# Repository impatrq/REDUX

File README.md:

2<div align="center">

</div>

<div align="center">

# REDUX: Órtesis activa de codo para rehabilitación traumatológica

</div>

<div align="center">

</div>

## 🔗 Repositorio y Redes:

## 🗓️ Objetivo del Proyecto:

El nombre **REDUX** proviene del latín y significa *"restauración"* o *"retorno"*. El objetivo general del proyecto es desarrollar un prototipo funcional, seguro y de costo accesible de órtesis activa de codo que asista los movimientos de flexión y extensión a partir de la señal electromiográfica de superficie (sEMG) del bíceps y del tríceps, con registro digital de cada sesión para su uso bajo supervisión profesional en consultorios de kinesiología.

## 🌎 Visión a futuro e Impacto esperado

REDUX busca ser una herramienta de apoyo para el kinesiólogo, no un reemplazo. Al asistir según el esfuerzo muscular real del paciente, reduce la fatiga, evita compensaciones musculares perjudiciales y permite registrar de forma objetiva la evolución (rango de movimiento y porcentaje de asistencia sesión a sesión). A futuro, la arquitectura abierta y accesible permite proyectar mejoras como control de posición, rutinas preprogramadas, extensión a otras articulaciones y ensayos con usuarios.

## 💭 ¿De dónde surgió la idea?

Los procesos de rehabilitación traumatológica del miembro superior (fracturas, luxaciones, traumatismos o cirugías) requieren numerosas sesiones repetitivas donde el profesional guía manualmente el brazo y registra mediciones puntuales, mientras que los exoesqueletos robóticos comerciales tienen costos elevados que dificultan su adopción en consultorios y centros de nuestra región. En el marco de las Prácticas Profesionalizantes de la especialidad Aviónica de la **E.E.S.T. N°7 "Taller Regional Quilmes" (IMPA)**, el equipo desarrolló una alternativa integral, segura y accesible.

## 🖐 Descripción del proyecto:

REDUX se compone de cuatro subsistemas físicos y una plataforma web remota:

* **Órtesis:** estructura impresa en 3D (diseño preliminar en Onshape y definitivo en AutoCAD) fijada a brazo y antebrazo mediante tiras elásticas y velcro, con topes mecánicos rígidos en la articulación y un encoder magnético absoluto **AS5600** (`I2C` a 400 kHz, 12 bits) que mide el ángulo articular.
* **Unidad de accionamiento:** motor de corriente continua de 12 V con reductora (30 RPM) montado externamente para reducir el peso en el brazo y aislar el ruido eléctrico, transmitiendo fuerza mediante un carrete y un sistema de poleas.
* **Unidad electrónica:** centrada en una **Raspberry Pi Pico 2 W (RP2350)** con firmware en **C11** sobre **Pico SDK 2.x** y lazo determinista de 1 ms (Núcleo 0 dedicado al control y Núcleo 1 a la interfaz). Integra dos cadenas analógicas de acondicionamiento sEMG (preamplificación con **AD620**, filtros activos Sallen-Key pasa-altos ~20 Hz y pasa-bajos ~500 Hz con **TL084**, rectificación de precisión de onda completa y circuito **RLD** con resistencia de seguridad de 4,7 a 10 MΩ), etapa de potencia con puente H **BTS7960** (PWM de 20 kHz) y aislación galvánica mediante optoacopladores **6N137**, separación de masas (`GND1` potencia y `GND2` lógica/señal) y fuentes aisladas (**LM2596** y **B0505S**).
* **Panel de control:** soporte inclinado a 35° con pantalla **TFT ST7735** (1,44", 128x128, `SPI1`) programada con **LVGL 8.3.11** (diseñada en SquareLine Studio) y teclado matricial de membrana **4x4**, comunicándose mediante colas para calibrar el rango articular y los umbrales de reposo/MVC en cada sesión, iniciar/finalizar sesiones y visualizar fallas o telemetría.
* **Plataforma web y gestión de datos:** aplicación **Flask** con **SQLite** y **SQLAlchemy**, interfaz en **HTML**, **Bootstrap 5** y **Chart.js**, autenticación con roles (`médico/kinesiólogo` y `paciente`), envío HTTP autenticado (`X-Redux-Key`) con `id_envio` idempotente y pruebas automáticas con `pytest`.

En operación, la lógica de intención evalúa la activación muscular mediante compuerta **XOR** entre bíceps y tríceps: asiste flexión o extensión de forma proporcional al esfuerzo y detiene/frena el motor ante reposo, co-contracción, límites articulares o fallas detectadas por la máquina de estados y el watchdog de 500 ms.

## 🛠️ Componentes principales:

| Componente | Función / Especificación |
| :--- | :--- |
| **Raspberry Pi Pico 2 W (RP2350)** | Microcontrolador principal (Cortex-M33, Wi-Fi, ADC interno, PWM, I2C, SPI) |
| **Encoder magnético AS5600** | Medición angular absoluta sin contacto de 12 bits vía I2C (0x36) |
| **Amplificadores de instrumentación AD620** | Preamplificación y ganancia diferencial de señales sEMG |
| **Amplificadores operacionales TL084** | Filtros activos pasa-altos/pasa-bajos, rectificador de precisión y RLD |
| **Electrodos descartables Ag/AgCl** | Adquisición superficial diferencial en bíceps y tríceps + referencia RLD |
| **Puente H BTS7960** | Control de motor DC 12 V (30 RPM) mediante señales PWM de 20 kHz |
| **Optoacopladores 6N137** | Aislación de señales PWM entre etapas de lógica y potencia |
| **Convertidores de alimentación / aislación** | LM2596, convertidor aislado B0505S y etapas ±5 V para analógica |
| **Pantalla TFT ST7735 + Teclado 4x4** | Interfaz local de calibración, control de sesión y diagnóstico |
| **Piezas impresas en 3D** | Estructura de órtesis, soporte de motor, carrete, caja electrónica y panel |

## 🧑🏽‍💻 Integrantes

| Integrantes | Responsabilidades | 
| :--- | :--- | 
| Bajales Ignacio | Gestion de Redes |
| Ramirez Hillz Benicio| Desarrollo de software |  
| Relañez Joaquin| Diseño de circuitos electronicos | 
| Gomez Facundo| Diseño de Placas electronicas | 
| Strangio Gael| Diseño 3D de eswtructura | 

## 🤝 Colaboración y Agradecimientos:

Este prototipo forma parte de las Prácticas Profesionalizantes de la especialidad Aviónica de la **E.E.S.T. N°7 "Taller Regional Quilmes" (IMPA)**. Agradecemos especialmente a nuestro sponsor, la **Universidad Argentina de la Empresa (UADE)**, por el asesoramiento, el espacio de trabajo y la impresión 3D de la estructura de la órtesis, así como a los docentes tutores y a toda la comunidad educativa.

Si deseas colaborar con **REDUX**, puedes aportar en:

- Perfeccionamiento del código y validaciones clínicas/técnicas.
- Mejora de hardware, PCB SMD y fabricación mecánica.
- Documentación técnica, manuales y ensayos de laboratorio.
- Apoyo institucional o financiero para investigación y desarrollo.

## 📱 Contactanos:

## 📱 Contactos personales

| Integrante | Gmail | LinkedIn |
| :--- | :--- | :--- |
| ** ** | | |
| ** ** | | |
| ** ** | | |
| ** ** | | |
| ** ** | | |

---

```[cite: 1, 5, 6, 7, 8, 9, 10, 11, 12, 13, 14, 15, 16, 17, 18, 19, 20, 21, 22, 23, 24, 25, 26, 27, 28, 29]

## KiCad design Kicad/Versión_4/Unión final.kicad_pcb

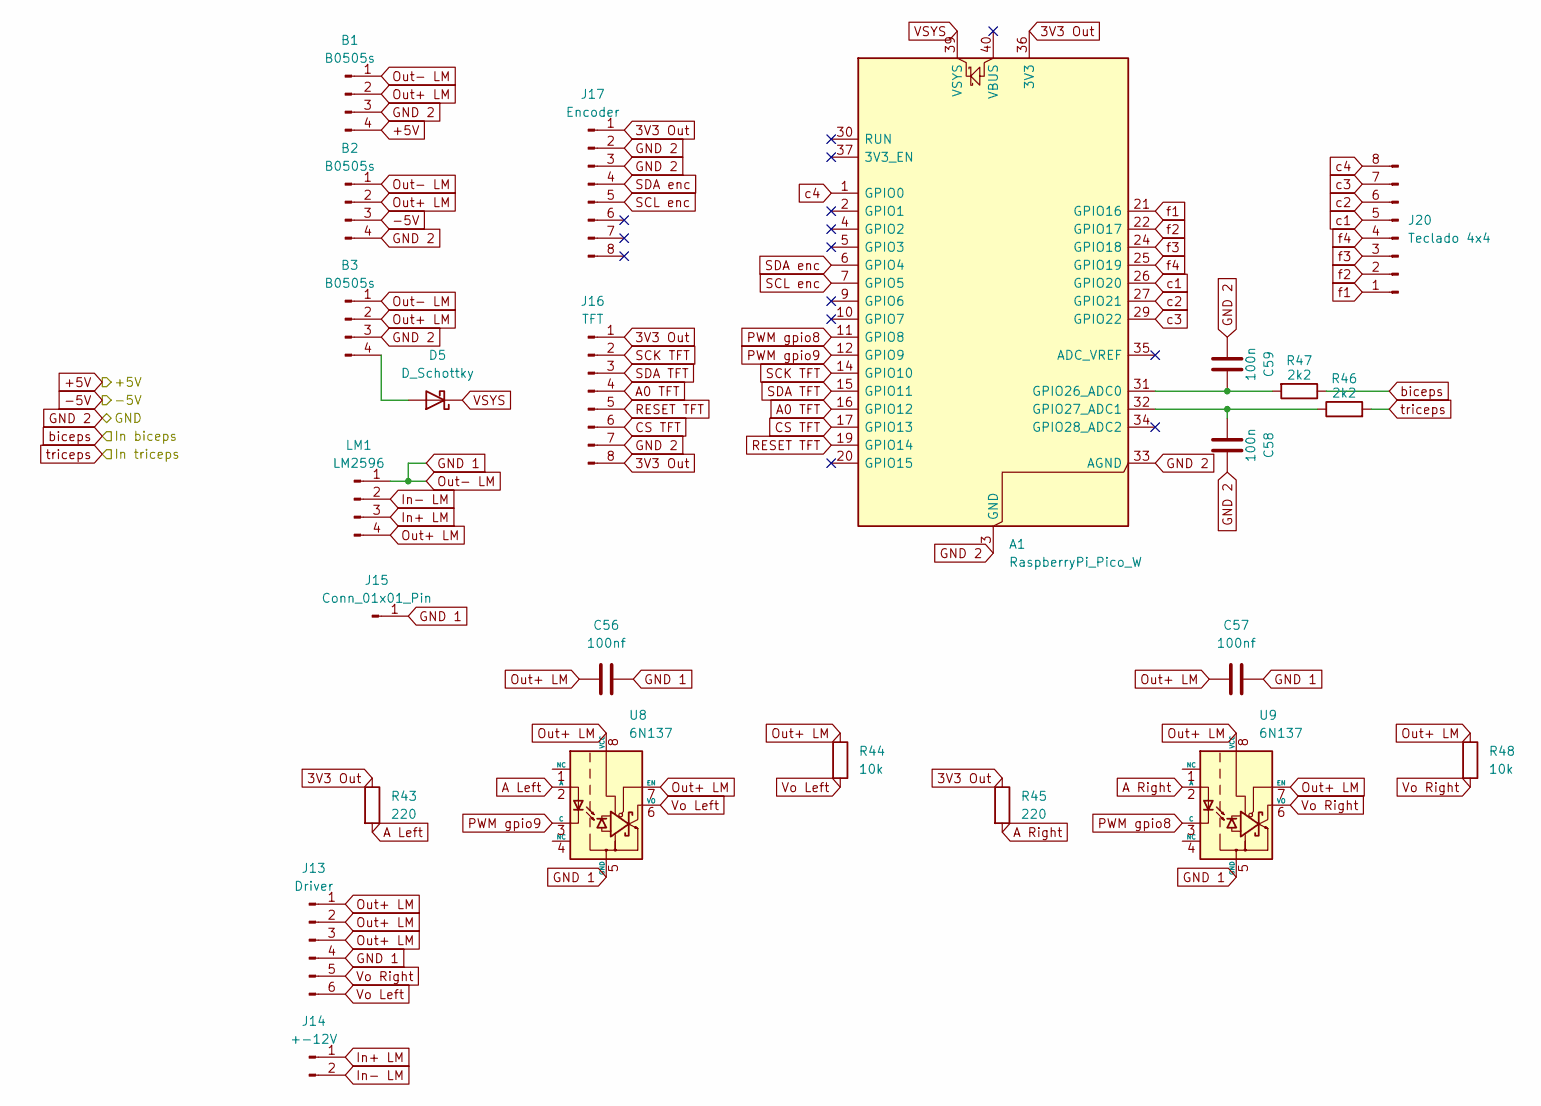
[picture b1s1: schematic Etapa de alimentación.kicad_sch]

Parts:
A1: RaspberryPi_Pico_W; RaspberryPi_Pico_Common_THT
B1, B2, B3: B0505s; B0505S-1w
C56, C57: 100nf; C_Disc_D10.0mm_W2.5mm_P5.00mm
C58, C59: 100n; C_0805_2012Metric_Pad1.18x1.45mm_HandSolder
D5: D_Schottky; D_DO-41_SOD81_P10.16mm_Horizontal
J13: Driver; PinHeader_1x06_P2.54mm_Vertical
J14: +-12V; TerminalBlock_MetzConnect_Type011_RT05502HBLC_1x02_P5.00mm_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
J15: Conn_01x01_Pin; PinHeader_1x01_P2.54mm_Vertical
J16: TFT; PinHeader_1x08_P2.54mm_Vertical
J17: Encoder; Molex_KK-254_AE-6410-08A_1x08_P2.54mm_Vertical
J20: Teclado 4x4; PinHeader_1x08_P2.54mm_Vertical
LM1: LM2596
R43, R45: 220; R_Axial_DIN0207_L6.3mm_D2.5mm_P10.16mm_Horizontal
R44, R48: 10k; R_Axial_DIN0207_L6.3mm_D2.5mm_P10.16mm_Horizontal
R46, R47: 2k2; R_Axial_DIN0207_L6.3mm_D2.5mm_P10.16mm_Horizontal
U8, U9: 6N137; DIP-8_W7.62mm

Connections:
3V3 Out: A1.36 (3V3), J16.1, J16.8, J17.1, R43.1, R45.1
+5V: B1.4; also elsewhere on the board
-5V: B2.3; also elsewhere on the board
A0 TFT: A1.16 (GPIO12), J16.4
A Left: R43.2, U8.2 (A)
A Right: R45.2, U9.2 (A)
CS TFT: A1.17 (GPIO13), J16.6
GND 1: B1.1, B2.1, B3.1, C56.2, C57.2, J13.4, J15.1 (Pin_1_1), LM1.1, U8.5 (GND), U9.5 (GND)
GND 2: A1.3 (GND), A1.8 (GND), A1.13 (GND), A1.18 (GND), A1.23 (GND), A1.28 (GND), A1.33 (AGND), A1.38 (GND), B1.3, B2.4, B3.3, C58.2, C59.1, J16.7, J17.2, J17.3; also elsewhere on the board
In+ LM: J14.1, LM1.3
In- LM: J14.2, LM1.2
unnamed: A1.31 (GPIO26_ADC0), C59.2, R47.2
unnamed: A1.32 (GPIO27_ADC1), C58.1, R46.1
unnamed: B3.4, D5.2 (A)
Out+ LM: B1.2, B2.2, B3.2, C56.1, C57.1, J13.1, J13.2, J13.3, LM1.4, R44.1, R48.1, U8.7 (EN), U8.8 (VCC), U9.7 (EN), U9.8 (VCC)
PWM gpio8: A1.11 (GPIO8), U9.3 (C)
PWM gpio9: A1.12 (GPIO9), U8.3 (C)
RESET TFT: A1.19 (GPIO14), J16.5
Rectificador biceps: R47.1; also elsewhere on the board
SCK TFT: A1.14 (GPIO10), J16.2
SCL enc: A1.7 (GPIO5), J17.5
SDA TFT: A1.15 (GPIO11), J16.3
SDA enc: A1.6 (GPIO4), J17.4
VSYS: A1.39 (VSYS), D5.1 (K)
Vo Left: J13.6, R44.2, U8.6 (VO)
Vo Right: J13.5, R48.2, U9.6 (VO)
c1: A1.26 (GPIO20), J20.5
c2: A1.27 (GPIO21), J20.6
c3: A1.29 (GPIO22), J20.7
c4: A1.1 (GPIO0), J20.8
f1: A1.21 (GPIO16), J20.1
f2: A1.22 (GPIO17), J20.2
f3: A1.24 (GPIO18), J20.3
f4: A1.25 (GPIO19), J20.4
triceps: R46.2; also elsewhere on the board

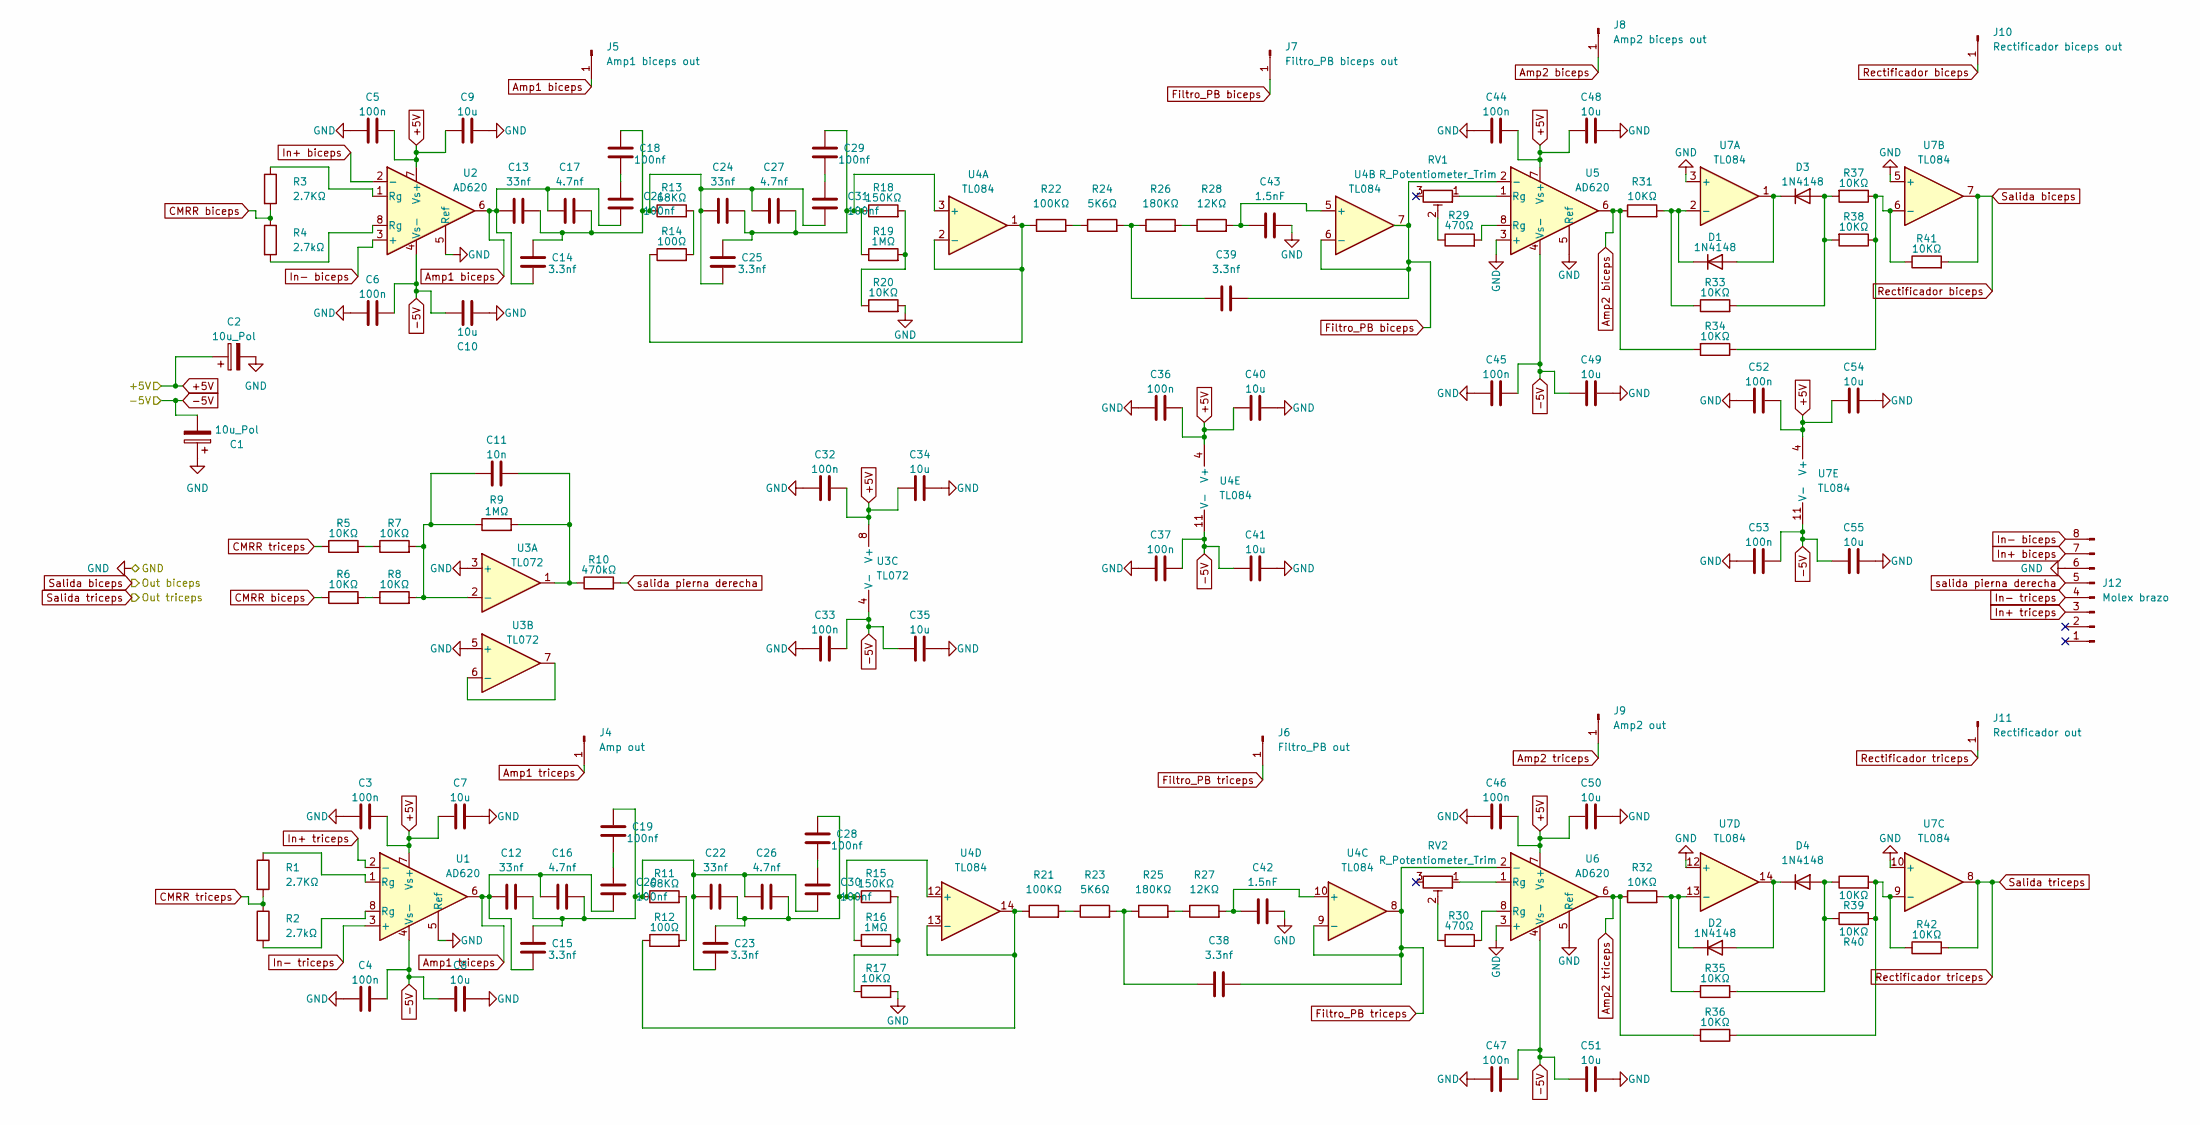
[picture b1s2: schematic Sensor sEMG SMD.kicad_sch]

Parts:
C1, C2: 10u_Pol; CP_Radial_D5.0mm_P2.00mm
C3, C4, C5, C6, C32, C33, C36, C37, C44, C45, C46, C47, C52, C53: 100n; C_0805_2012Metric_Pad1.18x1.45mm_HandSolder
C7, C8, C9, C10, C34, C35, C40, C41, C48, C49, C50, C51, C54, C55: 10u; C_0805_2012Metric_Pad1.18x1.45mm_HandSolder
C11: 10n; C_0805_2012Metric_Pad1.18x1.45mm_HandSolder
C12, C13, C22, C24: 33nf; C_0805_2012Metric_Pad1.18x1.45mm_HandSolder
C14, C15, C23, C25, C38, C39: 3.3nf; C_1206_3216Metric_Pad1.33x1.80mm_HandSolder
C16, C17, C26, C27: 4.7nf; C_1206_3216Metric_Pad1.33x1.80mm_HandSolder
C18, C19, C20, C21, C28, C29, C30, C31: 100nf; C_0805_2012Metric_Pad1.18x1.45mm_HandSolder
C42, C43: 1.5nF; C_0805_2012Metric_Pad1.18x1.45mm_HandSolder
D1, D2, D3, D4: 1N4148; D_SOD-123
J4: Amp out; PinHeader_1x01_P2.00mm_Vertical
J5: Amp1 biceps out; PinHeader_1x01_P2.00mm_Vertical
J6: Filtro_PB out; PinHeader_1x01_P2.00mm_Vertical
J7: Filtro_PB biceps out; PinHeader_1x01_P2.00mm_Vertical
J8: Amp2 biceps out; PinHeader_1x01_P2.00mm_Vertical
J9: Amp2 out; PinHeader_1x01_P2.00mm_Vertical
J10: Rectificador biceps out; PinHeader_1x01_P2.00mm_Vertical
J11: Rectificador out; PinHeader_1x01_P2.00mm_Vertical
J12: Molex brazo; Molex_KK-254_AE-6410-08A_1x08_P2.54mm_Vertical
R1, R3: 2.7KΩ; R_0805_2012Metric_Pad1.20x1.40mm_HandSolder
R2, R4: 2.7kΩ; R_0805_2012Metric_Pad1.20x1.40mm_HandSolder
R5, R6, R7, R8, R17, R20, R31, R32, R33, R34, R35, R36, R37, R38, R39, R40, R41, R42: 10KΩ; R_0805_2012Metric_Pad1.20x1.40mm_HandSolder
R9, R16, R19: 1MΩ; R_0805_2012Metric_Pad1.20x1.40mm_HandSolder
R10: 470kΩ; R_0805_2012Metric_Pad1.20x1.40mm_HandSolder
R11, R13: 68KΩ; R_1206_3216Metric_Pad1.30x1.75mm_HandSolder
R12, R14: 100Ω; R_0805_2012Metric_Pad1.20x1.40mm_HandSolder
R15, R18: 150KΩ; R_0805_2012Metric_Pad1.20x1.40mm_HandSolder
R21, R22: 100KΩ; R_1206_3216Metric_Pad1.30x1.75mm_HandSolder
R23, R24: 5K6Ω; R_1206_3216Metric_Pad1.30x1.75mm_HandSolder
R25, R26: 180KΩ; R_1206_3216Metric_Pad1.30x1.75mm_HandSolder
R27, R28: 12KΩ; R_1206_3216Metric_Pad1.30x1.75mm_HandSolder
R29, R30: 470Ω; R_0805_2012Metric_Pad1.20x1.40mm_HandSolder
RV1, RV2: R_Potentiometer_Trim; Potentiometer_Bourns_3296W_Vertical
U1, U2, U5, U6: AD620; SOIC-8_3.9x4.9mm_P1.27mm
U3: TL072; SOIC-8_3.9x4.9mm_P1.27mm
U4, U7: TL084; SOIC-14_3.9x8.7mm_P1.27mm

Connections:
+5V: C2.1, C3.2, C5.2, C7.1, C9.1, C32.2, C34.1, C36.2, C40.1, C44.2, C46.2, C48.1, C50.1, C52.2, C54.1, U1.7 (Vs+), U2.7 (Vs+), U3.8 (V+), U4.4 (V+), U5.7 (Vs+), U6.7 (Vs+), U7.4 (V+); also elsewhere on the board
-5V: C1.2, C4.2, C6.2, C8.1, C10.2, C33.2, C35.1, C37.2, C41.1, C45.2, C47.2, C49.1, C51.1, C53.2, C55.1, U1.4 (Vs-), U2.4 (Vs-), U3.4 (V-), U4.11 (V-), U5.4 (Vs-), U6.4 (Vs-), U7.11 (V-); also elsewhere on the board
Amp1 biceps: C13.1, C14.2, C17.1, C21.1, J5.1 (Pin_1_1), U2.6
Amp1 triceps: C12.1, C15.2, C16.1, C20.1, J4.1 (Pin_1_1), U1.6
Amp2 biceps: J8.1 (Pin_1_1), R31.1, R34.2, U5.6
Amp2 triceps: J9.1 (Pin_1_1), R32.1, R36.2, U6.6
CMRR biceps: R3.2, R4.1, R6.1
CMRR triceps: R1.2, R2.1, R5.1
Filtro_PB biceps: C39.2, J7.1 (Pin_1_1), U4.6 (-), U4.7, U5.2 (-)
Filtro_PB triceps: C38.2, J6.1 (Pin_1_1), U4.8, U4.9 (-), U6.2 (-)
GND 2: C1.1, C2.2, C3.1, C4.1, C5.1, C6.1, C7.2, C8.2, C9.2, C10.1, C32.1, C33.1, C34.2, C35.2, C36.1, C37.1, C40.2, C41.2, C42.2, C43.2, C44.1, C45.1, C46.1, C47.1, C48.2, C49.2, C50.2, C51.2, C52.1, C53.1, C54.2, C55.2, J12.6, R17.2, R20.2, U1.5 (Ref), U2.5 (Ref), U3.3 (+), U3.5 (+), U5.3 (+), U5.5 (Ref), U6.3 (+), U6.5 (Ref), U7.3 (+), U7.5 (+), U7.10 (+), U7.12 (+); also elsewhere on the board
In+ biceps: J12.7, U2.2 (-)
In+ triceps: J12.3, U1.2 (-)
In- biceps: J12.8, U2.3 (+)
In- triceps: J12.4, U1.3 (+)
unnamed: C11.2, R9.2, R10.1, U3.1
unnamed: C12.2, C15.1, C16.2, C19.1, C22.1, C23.2, C26.1, C30.1, R11.1
unnamed: C13.2, C14.1, C17.2, C18.1, C24.1, C25.2, C27.1, C31.1, R13.1
unnamed: C18.2, C21.2
unnamed: C19.2, C20.2
unnamed: C28.2, C30.2
unnamed: C29.2, C31.2
unnamed: C38.1, R23.2, R25.1
unnamed: C39.1, R24.2, R26.1
unnamed: D1.2 (A), D3.1 (K), U7.1
unnamed: D1.1 (K), R31.2, R33.1, U7.2 (-)
unnamed: D2.2 (A), D4.1 (K), U7.14
unnamed: D2.1 (K), R32.2, R35.1, U7.13 (-)
unnamed: D3.2 (A), R33.2, R37.2, R38.2
unnamed: D4.2 (A), R35.2, R39.1, R40.1
unnamed: R1.1, U1.1 (Rg)
unnamed: R2.2, U1.8 (Rg)
unnamed: R3.1, U2.1 (Rg)
unnamed: R4.2, U2.8 (Rg)
unnamed: R5.2, R7.1
unnamed: R6.2, R8.1
unnamed: R11.2, R12.2
unnamed: R13.2, R14.2
unnamed: R15.2, R16.2, R17.1
unnamed: R18.2, R19.2, R20.1
unnamed: R21.2, R23.1
unnamed: R22.2, R24.1
unnamed: R25.2, R27.1
unnamed: R26.2, R28.1
unnamed: R29.1, RV1.2
unnamed: R29.2, U5.8 (Rg)
unnamed: R30.1, RV2.2
unnamed: R30.2, U6.8 (Rg)
unnamed: RV1.1, U5.1 (Rg)
unnamed: RV2.1, U6.1 (Rg)
unnamed: C11.1, R7.2, R8.2, R9.1, U3.2 (-)
unnamed: U3.6 (-), U3.7
unnamed: C24.2, C25.1, C27.2, C29.1, R18.1, R19.1, U4.3 (+)
unnamed: R14.1, R22.1, U4.1, U4.2 (-)
unnamed: C43.1, R28.2, U4.5 (+)
unnamed: C42.1, R27.2, U4.10 (+)
unnamed: C22.2, C23.1, C26.2, C28.1, R15.1, R16.1, U4.12 (+)
unnamed: R12.1, R21.1, U4.13 (-), U4.14
unnamed: R34.1, R37.1, R38.1, R41.1, U7.6 (-)
unnamed: R36.1, R39.2, R40.2, R42.1, U7.9 (-)
Rectificador biceps: J10.1 (Pin_1_1), R41.2, U7.7; also elsewhere on the board
salida pierna derecha: J12.5, R10.2
triceps: J11.1 (Pin_1_1), R42.2, U7.8; also elsewhere on the board

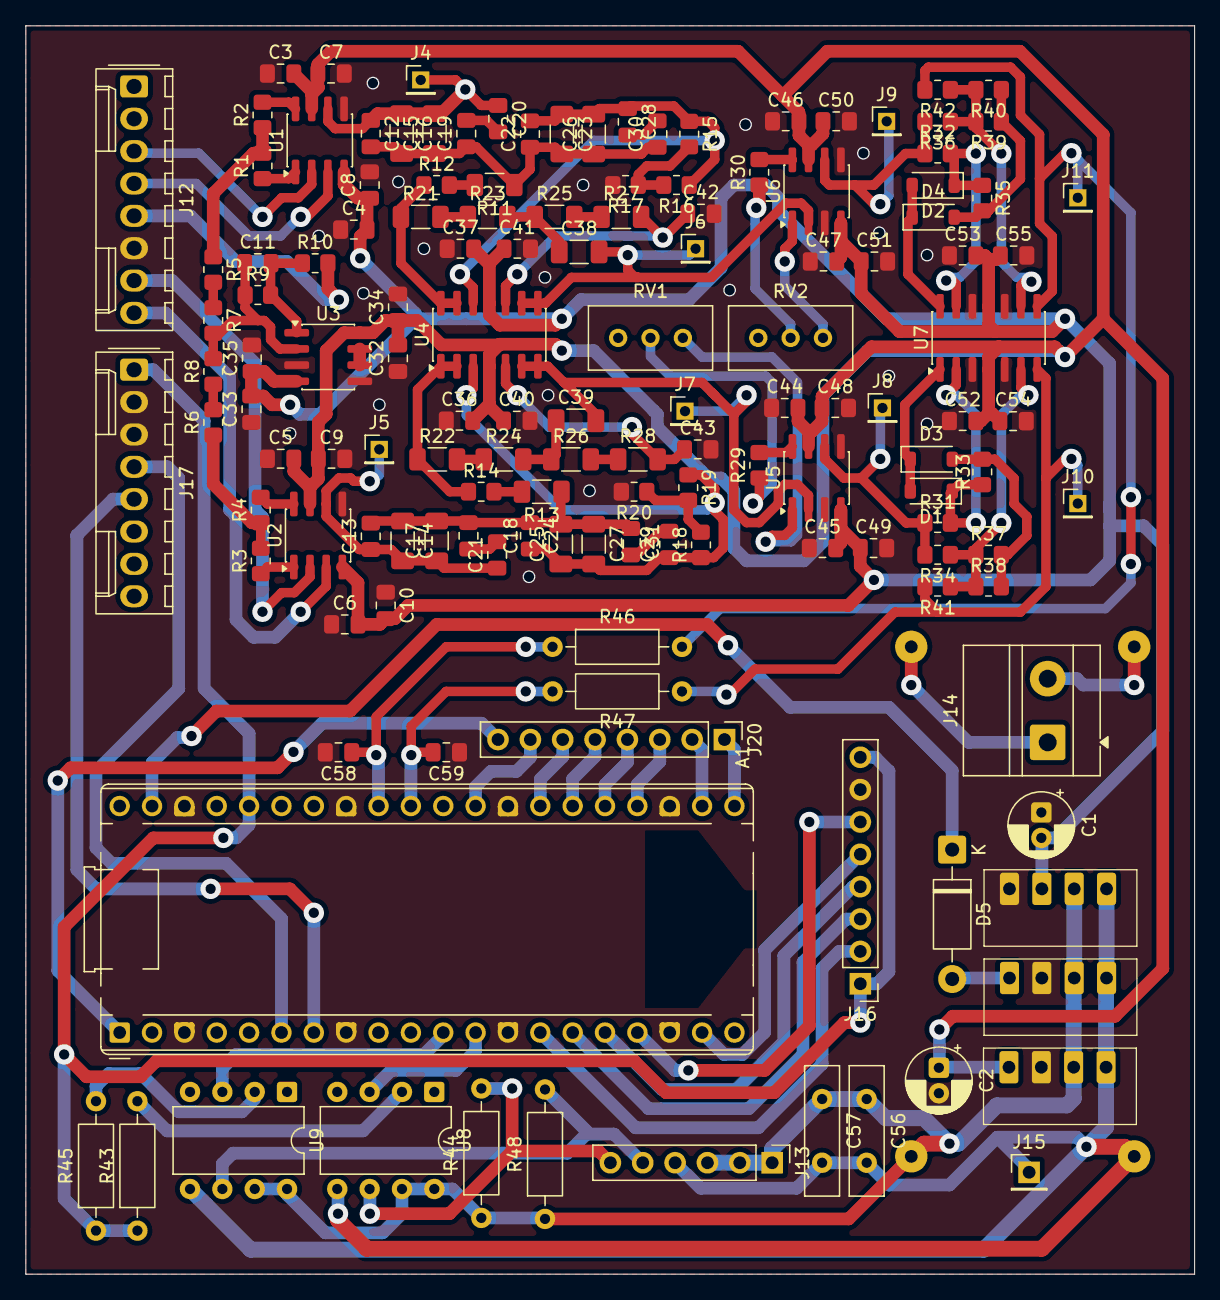
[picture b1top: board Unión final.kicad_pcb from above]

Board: 2 copper layers, 91.8 x 98.0 mm, 143 parts (1 on the bottom side), 93 nets.

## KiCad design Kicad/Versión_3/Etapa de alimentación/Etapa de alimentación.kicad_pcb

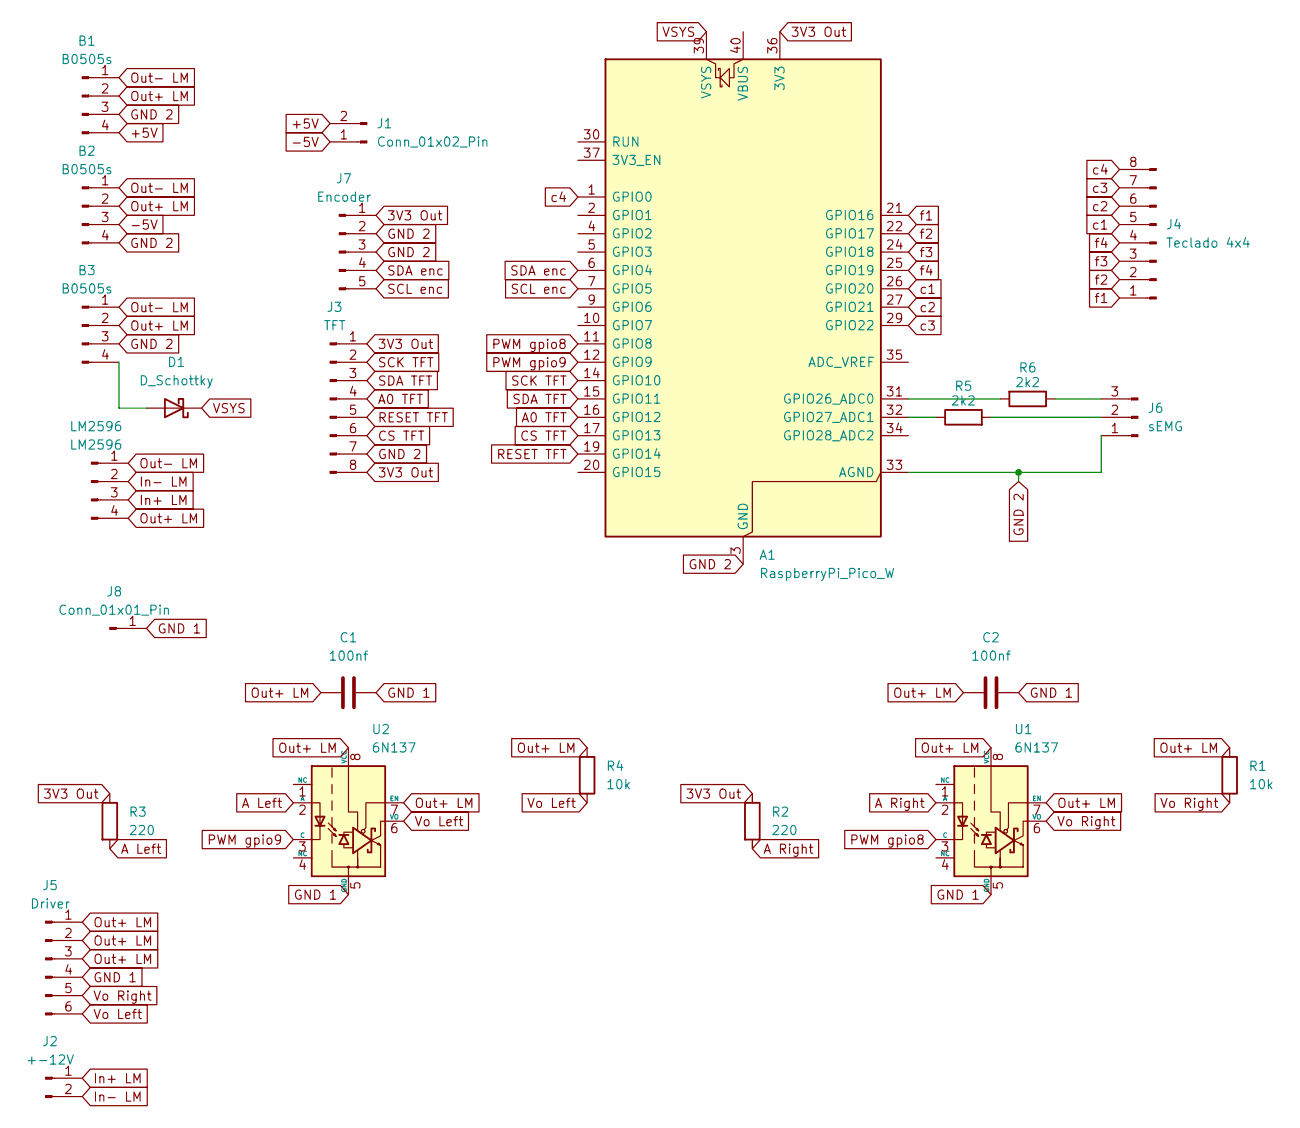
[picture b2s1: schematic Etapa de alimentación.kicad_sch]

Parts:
A1: RaspberryPi_Pico_W; RaspberryPi_Pico_Common_THT
B1, B2, B3: B0505s; B0505S-1w
C1, C2: 100nf; C_Disc_D10.0mm_W2.5mm_P5.00mm
D1: D_Schottky; D_5W_P12.70mm_Horizontal
J1: Conn_01x02_Pin; TerminalBlock_MetzConnect_Type011_RT05502HBLC_1x02_P5.00mm_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
J2: +-12V; TerminalBlock_MetzConnect_Type011_RT05502HBLC_1x02_P5.00mm_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
J3: TFT; PinHeader_1x08_P2.54mm_Vertical
J4: Teclado 4x4; PinHeader_1x08_P2.54mm_Vertical
J5: Driver; PinHeader_1x06_P2.54mm_Vertical
J6: sEMG; TerminalBlock_MetzConnect_Type011_RT05503HBLC_1x03_P5.00mm_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
J7: Encoder; TerminalBlock_MetzConnect_Type011_RT05505HBLC_1x05_P5.00mm_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
J8: Conn_01x01_Pin; PinHeader_1x01_P2.54mm_Vertical
LM2596: LM2596
R1, R4: 10k; R_Axial_DIN0207_L6.3mm_D2.5mm_P10.16mm_Horizontal
R2, R3: 220; R_Axial_DIN0207_L6.3mm_D2.5mm_P10.16mm_Horizontal
R5, R6: 2k2; R_Axial_DIN0207_L6.3mm_D2.5mm_P10.16mm_Horizontal
U1, U2: 6N137; DIP-8_W7.62mm

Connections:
3V3 Out: A1.36 (3V3), J3.1, J3.8, J7.1, R2.1, R3.1
+5V: B1.4, J1.2
-5V: B2.3, J1.1
A0 TFT: A1.16 (GPIO12), J3.4
A Left: R3.2, U2.2 (A)
A Right: R2.2, U1.2 (A)
CS TFT: A1.17 (GPIO13), J3.6
GND 1: C1.2, C2.2, J5.4, J8.1 (Pin_1_1), U1.5 (GND), U2.5 (GND)
GND 2: A1.3 (GND), A1.8 (GND), A1.13 (GND), A1.18 (GND), A1.23 (GND), A1.28 (GND), A1.33 (AGND), A1.38 (GND), B1.3, B2.4, B3.3, J3.7, J6.1, J7.2, J7.3
In+ LM: J2.1, LM2596.3
In- LM: J2.2, LM2596.2
unnamed: A1.31 (GPIO26_ADC0), R6.2
unnamed: A1.32 (GPIO27_ADC1), R5.1
unnamed: B3.4, D1.2 (A)
unnamed: J6.2, R5.2
unnamed: J6.3, R6.1
Out+ LM: B1.2, B2.2, B3.2, C1.1, C2.1, J5.1, J5.2, J5.3, LM2596.4, R1.1, R4.1, U1.7 (EN), U1.8 (VCC), U2.7 (EN), U2.8 (VCC)
Out- LM: B1.1, B2.1, B3.1, LM2596.1
PWM gpio8: A1.11 (GPIO8), U1.3 (C)
PWM gpio9: A1.12 (GPIO9), U2.3 (C)
RESET TFT: A1.19 (GPIO14), J3.5
SCK TFT: A1.14 (GPIO10), J3.2
SCL enc: A1.7 (GPIO5), J7.5
SDA TFT: A1.15 (GPIO11), J3.3
SDA enc: A1.6 (GPIO4), J7.4
VSYS: A1.39 (VSYS), D1.1 (K)
Vo Left: J5.6, R4.2, U2.6 (VO)
Vo Right: J5.5, R1.2, U1.6 (VO)
c1: A1.26 (GPIO20), J4.5
c2: A1.27 (GPIO21), J4.6
c3: A1.29 (GPIO22), J4.7
c4: A1.1 (GPIO0), J4.8
f1: A1.21 (GPIO16), J4.1
f2: A1.22 (GPIO17), J4.2
f3: A1.24 (GPIO18), J4.3
f4: A1.25 (GPIO19), J4.4

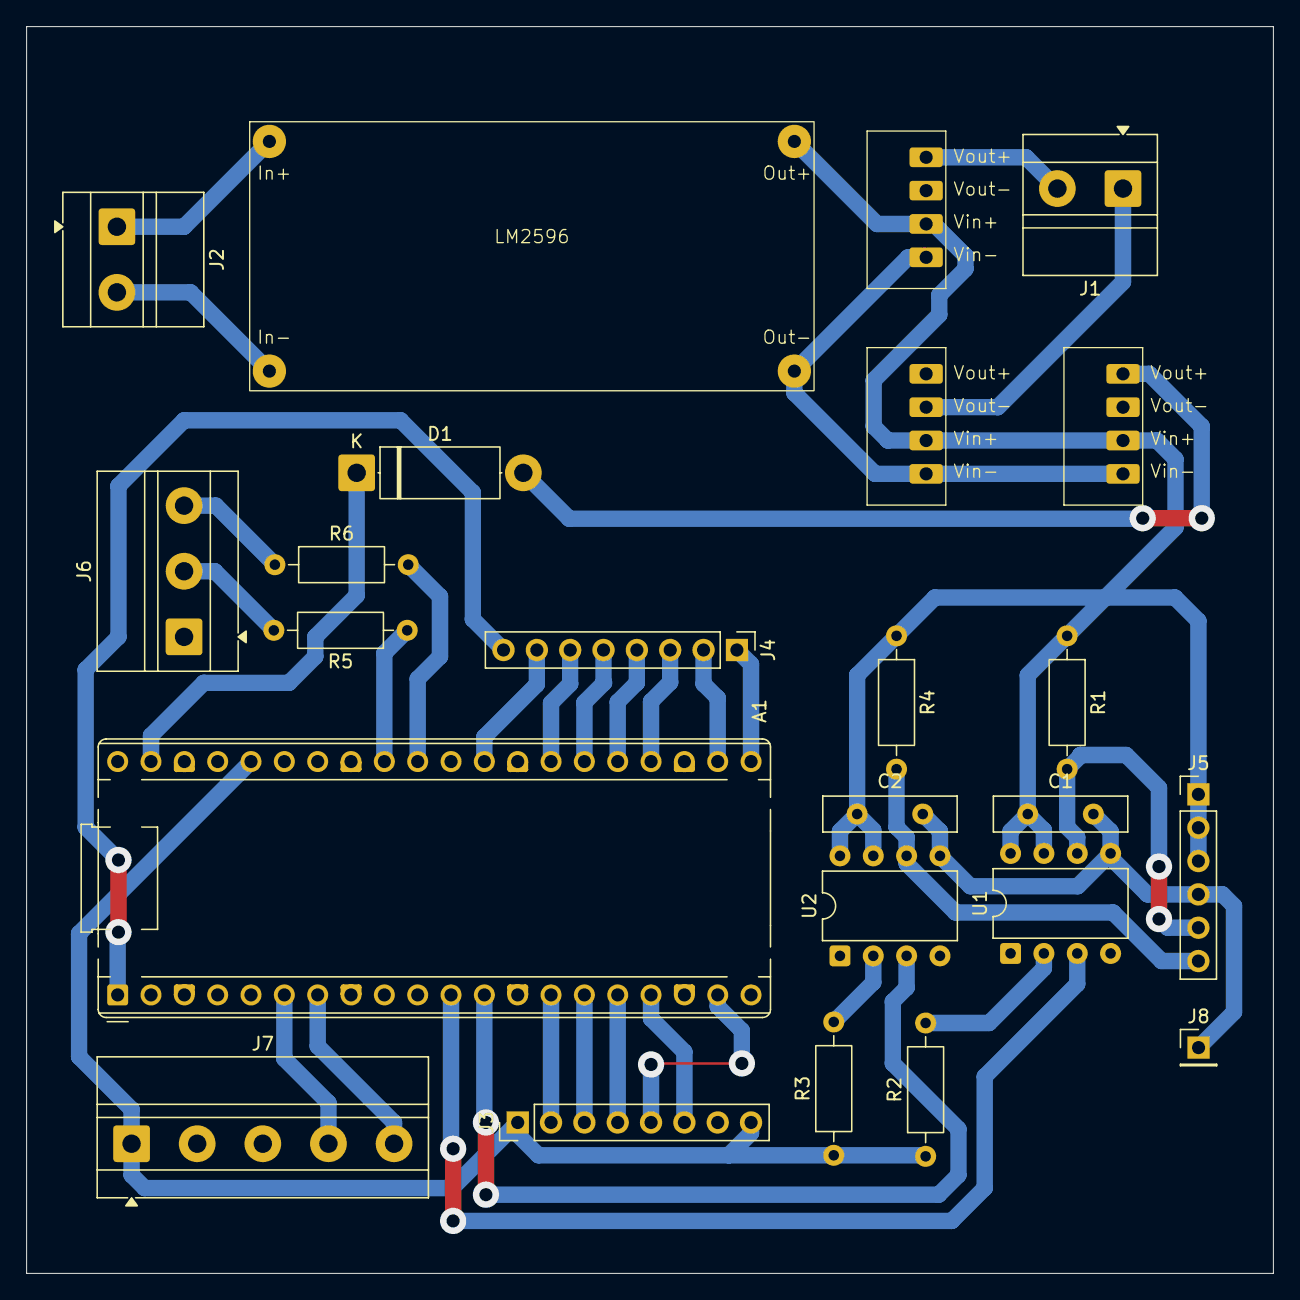
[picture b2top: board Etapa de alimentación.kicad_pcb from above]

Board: 2 copper layers, 95.0 x 95.0 mm, 24 parts (0 on the bottom side), 36 nets.

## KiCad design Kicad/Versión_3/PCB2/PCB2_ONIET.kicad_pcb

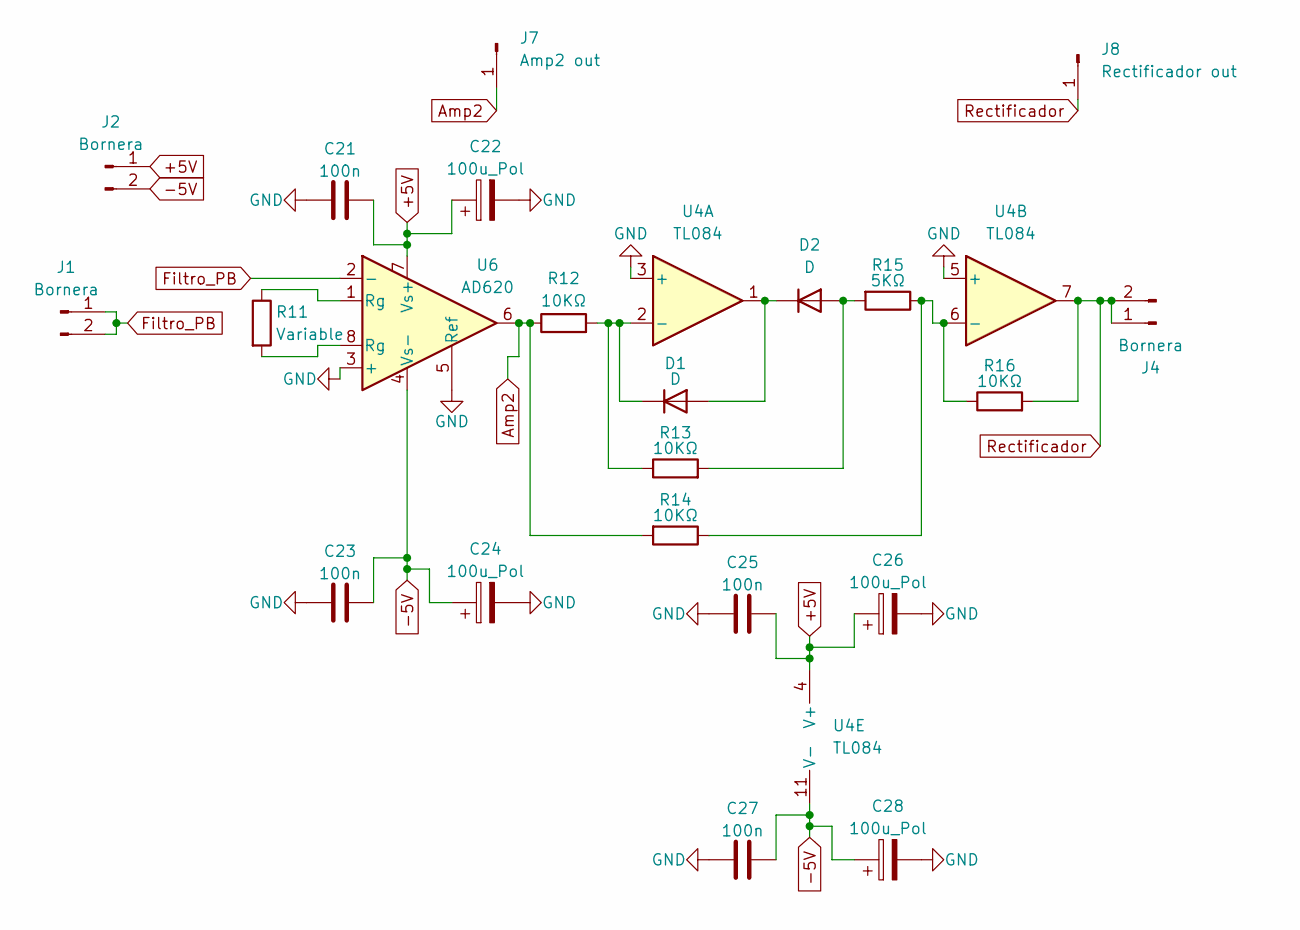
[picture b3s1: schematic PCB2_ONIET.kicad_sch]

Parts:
C21, C23, C25, C27: 100n; C_Disc_D10.5mm_W5.0mm_P10.00mm
C22, C24, C26, C28: 100u_Pol; C_Radial_D5.0mm_H11.0mm_P2.00mm
D1, D2: D; D_5W_P12.70mm_Horizontal
J1, J2, J4: Bornera; TerminalBlock_MetzConnect_Type011_RT05502HBLC_1x02_P5.00mm_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
J7: Amp2 out; PinHeader_1x01_P2.00mm_Vertical
J8: Rectificador out; PinHeader_1x01_P2.00mm_Vertical
R11: Variable; R_Axial_DIN0207_L6.3mm_D2.5mm_P10.16mm_Horizontal
R12, R13, R14, R16: 10KΩ; R_Axial_DIN0207_L6.3mm_D2.5mm_P10.16mm_Horizontal
R15: 5KΩ; R_Axial_DIN0207_L6.3mm_D2.5mm_P10.16mm_Horizontal
U4: TL084; DIP-14_W7.62mm_LongPads
U6: AD620; DIP-8_W7.62mm

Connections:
+5V: C21.2, C22.1, C25.2, C26.1, J2.1, U4.4 (V+), U6.7 (Vs+)
-5V: C23.2, C24.1, C27.2, C28.1, J2.2, U4.11 (V-), U6.4 (Vs-)
Amp2: J7.1 (Pin_1_1), R12.1, R14.2, U6.6
Filtro_PB: J1.1, J1.2, U6.2 (-)
GND: C21.1, C22.2, C23.1, C24.2, C25.1, C26.2, C27.1, C28.2, U4.3 (+), U4.5 (+), U6.3 (+), U6.5 (Ref)
unnamed: D1.2 (A), D2.1 (K), U4.1
unnamed: D1.1 (K), R12.2, R13.1, U4.2 (-)
unnamed: D2.2 (A), R13.2, R15.2
unnamed: R11.1, U6.1 (Rg)
unnamed: R11.2, U6.8 (Rg)
unnamed: R14.1, R15.1, R16.1, U4.6 (-)
Rectificador: J4.1, J4.2, J8.1 (Pin_1_1), R16.2, U4.7

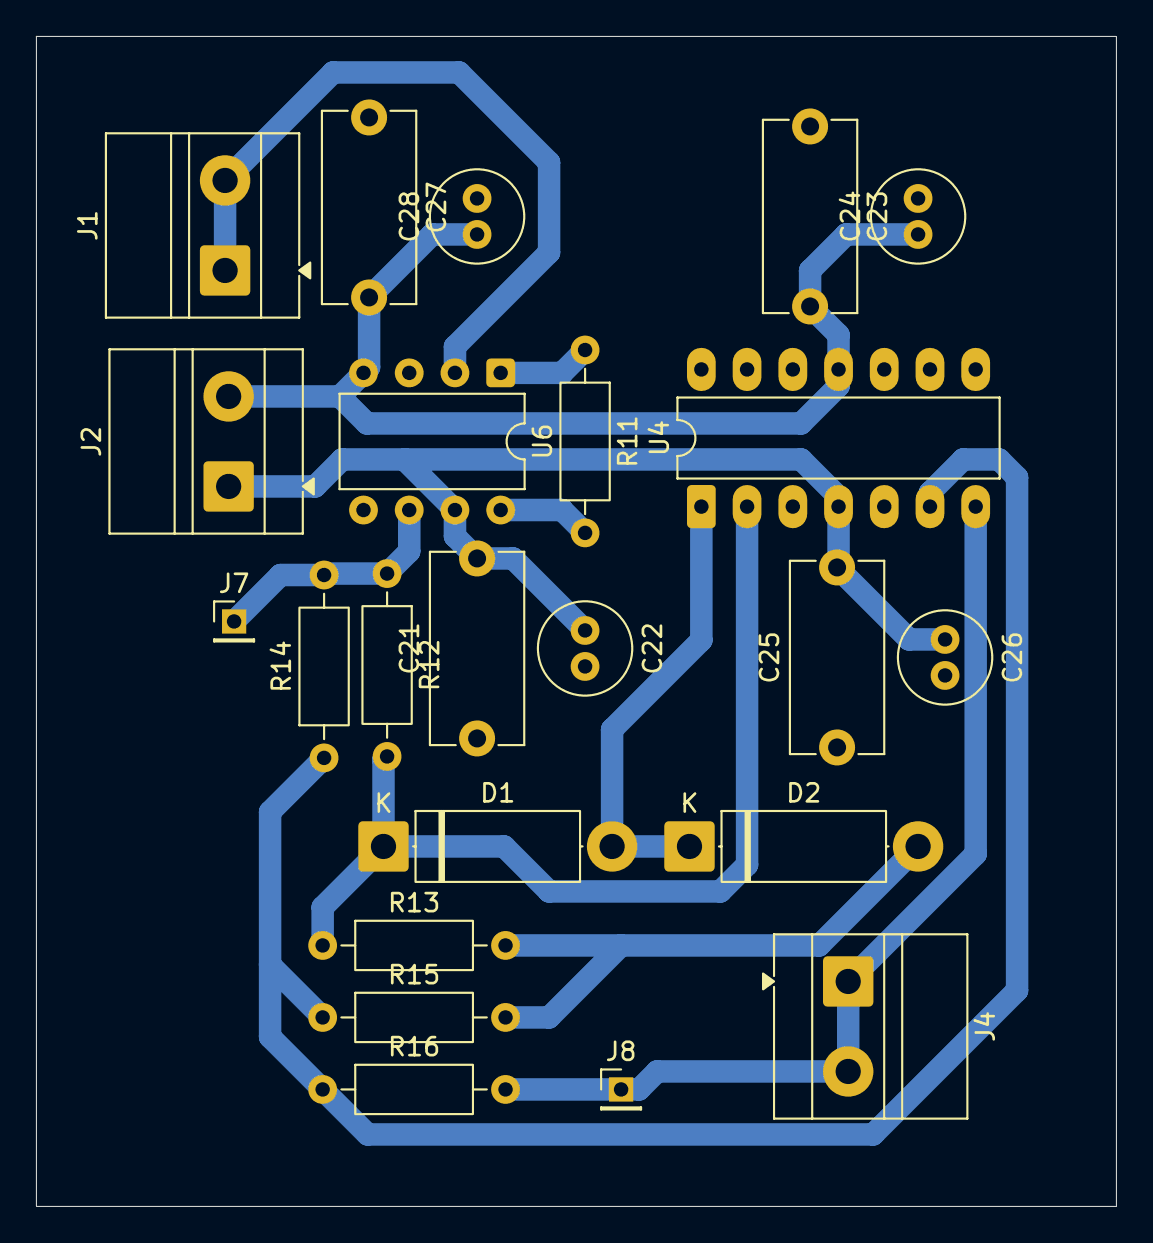
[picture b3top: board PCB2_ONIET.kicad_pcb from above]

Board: 2 copper layers, 60.0 x 65.0 mm, 23 parts (0 on the bottom side), 12 nets.

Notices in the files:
README.md:
License: MIT
